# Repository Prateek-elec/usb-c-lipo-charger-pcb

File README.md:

<div align="center">

**A 19 × 30 mm USB-C charger and protection board for single-cell Li-ion / LiPo batteries: 1 A charging, with over-charge, over-discharge and short-circuit protection.**

</div>

---

## The board

<table>
<tr>
<td width="50%" align="center"><br/><sub><b>Top:</b> USB-C in at the top, TP4056 (U1) on the left, DW01A (U2) and FS8205A (Q1) protection on the right, battery connector at the bottom</sub></td>
<td width="50%" align="center"><br/><sub><b>Bottom:</b> ground pour, stitching vias and the USB-C shell tabs</sub></td>
</tr>
</table>

<sub>Rendered from the design files. The footprints have no 3D models, so parts show as their pads.</sub>

## How it works

```text
 USB-C 5 V ──► TP4056 ──► BAT+ ─────────────────────────────► battery (+)
   CC1/CC2      │  1 A CC/CV to 4.2 V                          
   5.1 kΩ ↓     ├─ CHRG LED  (charging)                       
                └─ STDBY LED (done)                            
                                                               
 battery (−) ──► FS8205A dual MOSFET ──► BAT− / output (−)
                    ▲ gates
                 DW01A protection IC (watches cell voltage and current)
```

- **Charging (U1, TP4056):** a linear charger with constant-current then constant-voltage charging to 4.2 V. The 1.2 kΩ PROG resistor (R2) sets the charge current to **1 A** (I = 1200 / R<sub>PROG</sub>). Two LEDs show *charging* and *done*.
- **Protection (U2 DW01A + Q1 FS8205A):** the DW01A watches the cell and switches the low-side MOSFET pair off on over-charge (~4.3 V), over-discharge (~2.4 V), over-current and short circuit. The 100 Ω / 100 nF pair (R5, C3) filters its supply.
- **USB-C done right (R6, R7):** 5.1 kΩ pull-downs on both CC pins mark the board as a power sink, so **USB-C-to-C chargers will actually supply 5 V**. Many cheap USB-C charger boards leave these out and only work with A-to-C cables.
- **Connectors:** JST GH 1.25 mm for the battery (CN2), and a 1.27 mm header (H1) for the protected output.

## Specs

| | |
|---|---|
| **Input** | 5 V over USB Type-C (A-to-C and C-to-C cables) |
| **Battery** | 1 cell Li-ion / LiPo, 4.2 V full charge |
| **Charge current** | 1 A (change R2 to adjust: 2 kΩ ≈ 580 mA, 10 kΩ ≈ 130 mA) |
| **Protection** | Over-charge, over-discharge, over-current, short circuit |
| **Board** | About 19 × 30 mm, 2 layers, all parts on the top side |
| **Parts** | 18, see [BOM.csv](BOM.csv) |

## Files

| Path | What it is |
|---|---|
| [`pads/usb-c-charger.asc`](pads/usb-c-charger.asc) | Board in **PADS ASCII** (opens in PADS / PADS Professional, imports into Altium and KiCad) |
| [`pads/usb-c-charger-schematic.txt`](pads/usb-c-charger-schematic.txt) | Schematic in **PADS Logic ASCII** |
| [`pads/library-*.c`, `library-*.d`](pads/) | The schematic symbols and PCB footprints used |
| [`kicad/usb-c-charger.kicad_pcb`](kicad/usb-c-charger.kicad_pcb) | The board converted to KiCad, to view and edit for free |
| [`BOM.csv`](BOM.csv) | Bill of materials with what each part does |

The schematic was captured in EasyEDA Pro and the board laid out in PADS Professional.

> **Before ordering:** the KiCad conversion has no board outline (Edge.Cuts), so draw one around the copper pour or generate Gerbers from the PADS file. Check the TP4056's thermal pad is soldered: at 1 A it dissipates up to ~1 W.

## License

[MIT](LICENSE) © Prateek Sarkar

---

<div align="center">

**If this saved you a design, give it a ⭐.** More boards: [github.com/Prateek-elec](https://github.com/Prateek-elec)

</div>

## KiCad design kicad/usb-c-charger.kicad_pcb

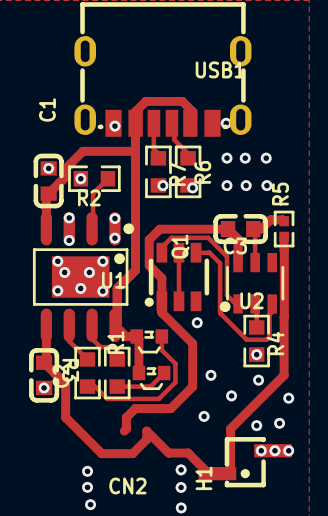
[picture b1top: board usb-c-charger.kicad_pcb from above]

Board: 2 copper layers, 18 parts (0 on the bottom side), 16 nets.

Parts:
C1, C2: CL10A106MA8NRNC; C0603
C3: CT41G-0603-2X1-50V-0.1uF-K(N); C0603
CN2: GH1.25-2PLT
H1: PZ1.27-1x2PLT-L7.2-R_Pin_header; HDR-SMD_2P-P1.27-V-M-LS4.2-R1
LED1, LED2: YLED0602RSIDE; LED-SMD_L1.6-W1.1-RD
Q1: FS8205A_C2830320; SOT-23-6_L2.9-W1.6-P0.95-LS2.8-BR
R1, R3, R4: RC0603FR-071KL; R0603
R2: 0603WAF1201T5E; R0603
R5: RC0402FR-07100RL; R0402
R6, R7: 0603WAF5101T5E; R0603
U1: TP4056_C20199357; ESOP-8_L4.9-W3.9-P1.27-LS6.0-BL-EP-4
U2: DW01A_C351410; SOT-23-6_L2.9-W1.6-P0.95-LS2.8-BL
USB1: TYPE-C_6P_C53207798; USB-C-SMD_HX-TYPE-C-6PIN

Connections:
$1N10: LED1.1, R1.2
$1N11: LED2.1, R3.2
$1N23: R4.2, U2.2
$1N25: Q1.6, U2.1
$1N26: Q1.4, U2.3
$1N36: C3.2, R5.1, U2.5
$1N37: Q1.2, Q1.5
$1N46: R6.2, USB1.A5
$1N47: R7.2, USB1.B5
CHRG: R1.1, U1.7
GND: C1.1, C2.1, H1.2, Q1.3, R2.1, R4.1, R6.1, R7.1, U1.1, U1.3, U1.9, USB1.13, USB1.14, USB1.15, USB1.16, USB1.A12, USB1.B12
PROG: R2.2, U1.2
STDBY: R3.1, U1.6
VBAT_N: C3.1, Q1.1, U2.6
VBAT_P: C2.2, H1.1, R5.2, U1.5
VIN: C1.2, LED1.2, LED2.2, U1.4, U1.8, USB1.A9, USB1.B9

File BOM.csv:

Ref,Qty,Part,Function,Package
U1,1,TP4056,1 A linear Li-ion charger (CC/CV to 4.2 V),ESOP-8 with thermal pad
U2,1,DW01A,Battery protection: over-charge / over-discharge / over-current / short,SOT-23-6
Q1,1,FS8205A,Dual N-MOSFET switched by the DW01A,SOT-23-6
USB1,1,USB Type-C 6-pin receptacle,5 V input,SMD
R6 R7,2,5.1 kΩ,USB-C CC pull-downs (lets C-to-C chargers supply 5 V),0603
R2,1,1.2 kΩ,TP4056 PROG resistor: sets 1 A charge current,0603
R1 R3 R4,3,1 kΩ,LED current limiting / DW01A current sense,0603
R5,1,100 Ω,DW01A supply filter,0402
C1 C2,2,10 µF,Input and battery bypass,0603
C3,1,100 nF,DW01A supply filter,0603
LED1 LED2,2,Red LED,Charging / done indicators,1608
CN2,1,JST GH 1.25 mm 2-pin,Battery connector,SMD
H1,1,1.27 mm 2-pin header,Protected battery output,SMD
